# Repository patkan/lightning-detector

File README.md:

lightning-detector
==================

Lightning Detector ethernet sensor node and server based on AS3935 and ATmega328

by Virtex7 and patkan

<h3>Structure</h3>

server: Server-Software
    
pcb: KiCAD-Schematic and Layout

code: Code for the node

<h3>Aim</h3>

The aim of this project is to develop a network of sensors.
Those mainly detect lightning events, their intensity and distance.
As an addition the sensor nodes might capture weather data (light level, humidity, temperature, maybe pressure).

The captured data is then transferred to a single server together with a timestamp and the position of the node.
This server tries to determine the exact position of the lightning events by triangulation.
In further steps the server could generate maps and lists of lightning events.

The captured data shall be accessible to everyone without registration.
New sensors should be able to "join" the network by simply sending data to the server.
The server will provide the raw sensor data and the correlated values.
The complete project code (including microcontroller firmware and aggregation server) and board layout will be distributed under an open source license.

This project tries to be different from blitzortung.org. The code and layout shall be easily accesible.
The captured data shall be accessible for everyone (even if the user is not providing sensor data).
The hardware necessary for the absolute basic setup should not cost more than 25€ - 30€.
Everyone is free to use the data commercially, if desired.
However, it should be noted that no one can be taken liable for the correctness of the captured data.

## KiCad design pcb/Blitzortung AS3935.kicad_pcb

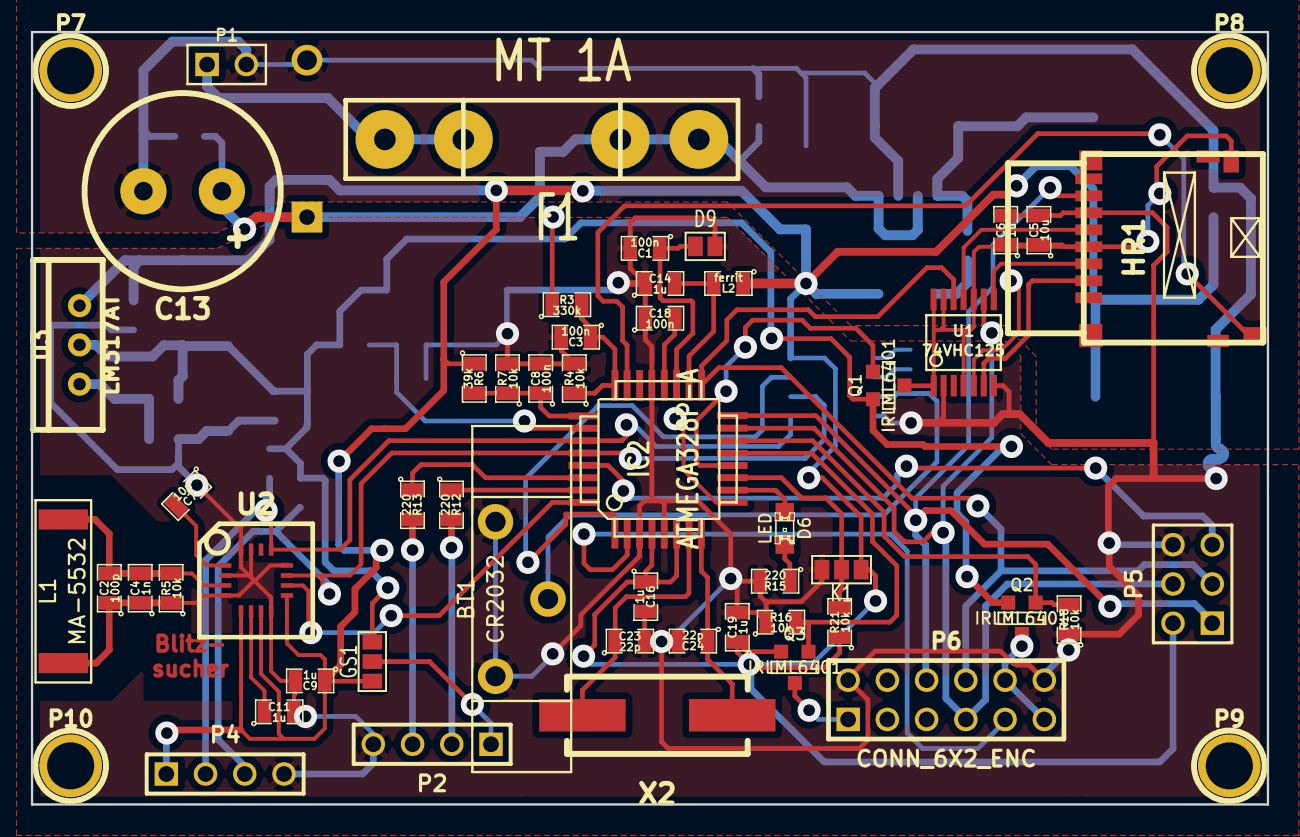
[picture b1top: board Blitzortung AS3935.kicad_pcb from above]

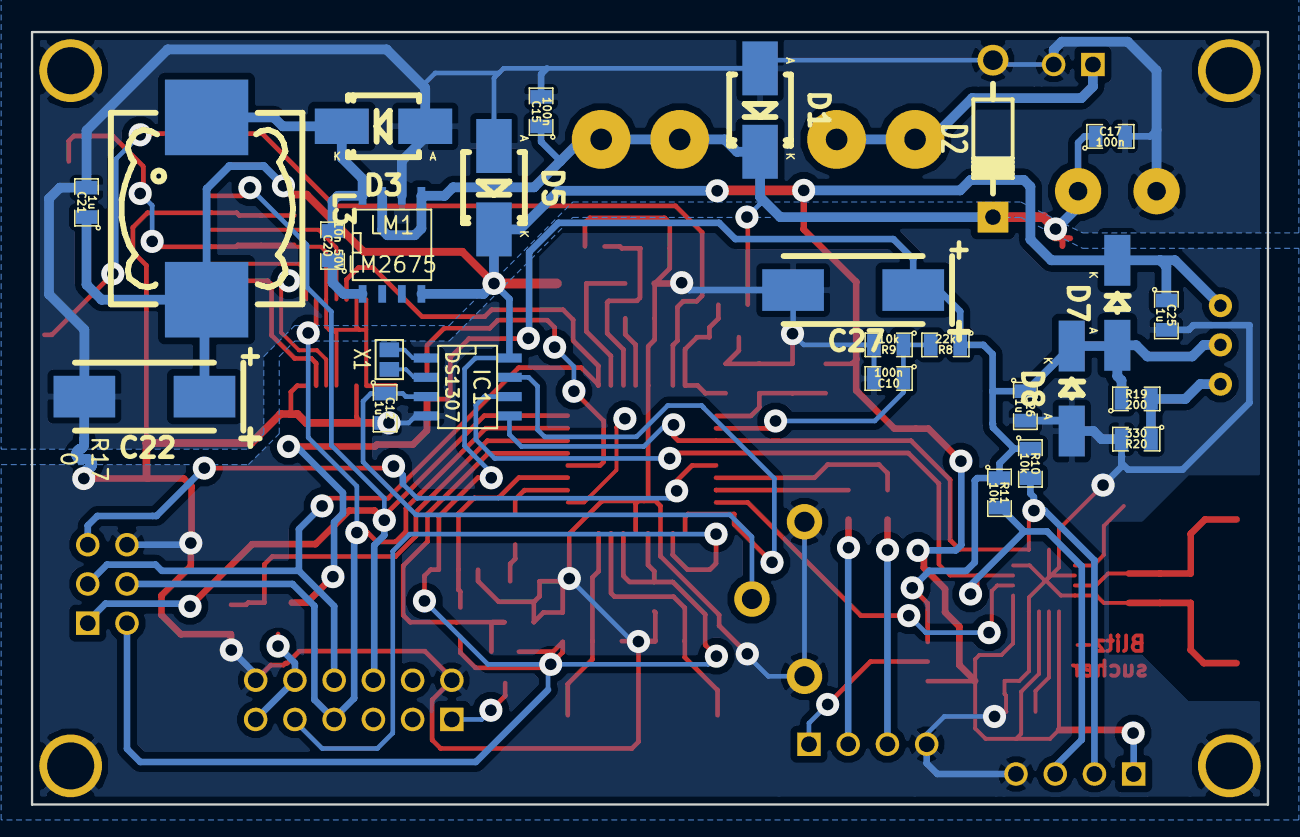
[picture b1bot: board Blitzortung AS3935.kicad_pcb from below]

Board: 2 copper layers, 80.0 x 50.0 mm, 81 parts (27 on the bottom side), 51 nets.

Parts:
BT1: CR2032; KHZ 20PCB-V
C1, C3, C8, C10, C15, C17, C18: 100n; SM0805
C2: 100p; SM0805
C4: 1n; SM0805
C5, C7: 10u; SM0805
C6, C9, C11, C12, C14, C16, C19, C21, C25, C26: 1u; SM0805
C13: 470u; Elko_vert_DM12-5_RM5
C20: 10n 50V; SM0805
C22, C27: 47u Tantal; TantalC_SizeD_EIA-7343_HandSoldering_RevA_28Aug2012
C23, C24: 22p; SM0805
D1: p6ke39aSMD; Diode-SMB_Handsoldering_RevA_27July2010
D2: SB150; Diode_DO-41_SOD81_Horizontal_RM10
D3: PMEG6030; Diode-SMB_Handsoldering_RevA_27July2010
D5: p6ke6,8aSMD; Diode-SMB_Handsoldering_RevA_27July2010
D6: LED; LED-0805
D7: 1n4148; Diode-MiniMELF_Handsoldering_RevA_27July2010
D8: zf3,6SMD; Diode-MiniMELF_Handsoldering_RevA_27July2010
D9: BPW34; GS2
F1: MT 1A; FUSE5-20
GS1: GS3
HR1: DM3D-SF
IC1: DS1307; SOIC-8_N
IC2: ATMEGA328P-A; TQFP32
K1: CONN_3_DHT; GS3
L1: MA-5532; MA5532-AE
L2: ferrit; SM0805
L3: 68uH; Choke_SMD_Wuerth-WE-PD-Typ-LS_Handsoldering_RevA_27July2010
LM1: LM2675; SO8N
P1: CONN_2_pwr; PIN_ARRAY_2X1
P2: CONN_4_GPS; PIN_ARRAY_4x1
P4: CONN_4_I2C; PIN_ARRAY_4x1
P5: CONN_3X2_ISP; pin_array_3x2
P6: CONN_6X2_ENC; pin_array_6x2
P7, P8, P9, P10: CONN_1; 1pin
Q1, Q2, Q3: IRLML6401; SOT23GDS
R3: 330k; SM0805
R4, R5, R7, R9, R10, R11, R16, R18, R21: 10k; SM0805
R6: 39k; SM0805
R8: 22k; SM0805
R12, R13, R15: 220; SM0805
R17: 0; MuSelf
R19: 200; SM0805
R20: 330; SM0805
U1: 74VHC125; SSOP-14
U2: AS3935; QFN-16-P
U3: LM317AT; TO220_VERT_123
X1: Uhrenquarz; GS2
X2: 20MHz; Crystal_HC49-SD_SMD_RevA_09Aug2010

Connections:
+3.3V: C26.1, C27.1, D7.1, D8.2, GS1.3, Q1.S, Q2.S, R8.1, R10.1, R11.1, R19.1, U3.2
+5V: C9.1, C16.1, C19.1, C21.1, C22.1, C25.1, D5.2, D7.2, GS1.1, IC1.8, IC2.4, IC2.6, K1.1, L2.1, L3.2, LM1.4, P4.1, P5.2, Q3.S, R6.1, R21.1, U2.5, U2.7, U2.9, U3.3
/IRQ_AS: IC2.32, U2.10
/IRQ_RTC: IC1.7, IC2.1
/IRQ_SD: HR1.10, IC2.23
/Vldr: C1.1, D9.1, IC2.19
/clk: HR1.5, U1.11
/cs: HR1.2, U1.6
/dht: IC2.11, K1.2, R21.2
/di: HR1.3, U1.8
/eth_3V: IC2.14, Q2.G, R18.2
/eth_5V: IC2.13, Q3.G, R16.2
/eth_cs: IC2.2, P6.9
/eth_res: P6.10, P6.11, Q2.D
/eth_sck: IC2.17, P5.3, P6.8, U1.12
/eth_si: IC2.15, P5.4, P6.7, U1.9
/eth_so: HR1.7, IC2.16, P5.1, P6.6
/mess3,3V: C10.1, IC2.26, R8.2, R9.1
/mess5V: C8.1, IC2.25, R6.2, R7.1
/messVin: C3.1, IC2.24, R3.2, R4.1
/reset: IC2.29, P5.5
/rxd: IC2.30, R13.1
/scl: IC1.6, IC2.28, P4.3, R11.2, U2.11
/sd3,3V: IC2.12, Q1.G
/sd_cs: IC2.9, U1.5
/sda: IC1.5, IC2.27, P4.2, R10.2, U2.13
/txd: IC2.31, R12.1
/xtal1: C23.1, IC2.7, X2.2
/xtal2: C24.1, IC2.8, X2.1
GND: BT1.2, C1.2, C2.1, C3.2, C4.1, C5.2, C6.2, C7.1, C8.2, C9.2, C10.2, C11.2, C12.2, C14.1, C16.2, C18.1, C19.2, C23.2, C24.2, C25.2, C26.2, C27.2, D8.1, D9.2, HR1.6, IC1.4, IC2.3, IC2.5, IC2.21, K1.3, L1.2, P2.4, P4.4, P5.6, P6.2, P6.12, P9.1, P10.1, R4.2, R5.1, R7.2, R9.2, R15.2, R16.1, R17.1, R18.1, R20.2, U1.2, U1.7, U2.2, U2.4, U2.8, U2.12, U2.15, U2.16
GNDPWR: C13.2, C15.2, C17.2, C21.2, C22.2, D1.1, D2.1, D3.1, D5.1, LM1.6, P1.2, P7.1, P8.1, R17.2
unnamed: BT1.1, C12.1, IC1.3
unnamed: C2.2, C4.2, L1.1, R5.2, U2.3
unnamed: C7.2, U2.1
unnamed: C11.1, U2.6
unnamed: C13.1, C15.1, C17.1, D1.2, D2.2, F1.2, LM1.5, LM1.7, R3.1
unnamed: C14.2, IC2.18, L2.2
unnamed: C18.2, IC2.20
unnamed: C20.1, LM1.1
unnamed: C20.2, D3.2, L3.1, LM1.8
unnamed: D6.1, IC2.10
unnamed: D6.2, R15.1
unnamed: F1.1, P1.1
unnamed: GS1.2, P2.1
unnamed: IC1.1, X1.2
unnamed: IC1.2, X1.1
unnamed: P2.2, R12.2
unnamed: P2.3, R13.2
unnamed: P6.1, Q3.D
unnamed: R19.2, R20.1, U3.1
VCC: C5.1, C6.1, HR1.4, HR1.9, Q1.D, U1.1, U1.4, U1.10, U1.13, U1.14

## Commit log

2013-11-07 Update README.md
    Grobe Übersicht angelegt
2013-11-07 base structure for project
2013-11-07 ideas for the project
2013-11-08 new CAD Files for lightning-detector, in progress....
2013-11-08 added Antenna
2013-11-08 AGC to ACG
2013-11-08 ignoring .ps and .bak files from KiCAD
2013-11-08 Directory for app notes, datasheets and other ressources
2013-11-08 datasheets of antenna and detector chip
2013-11-08 Atmel datasheet
2013-11-08 typo in filename
2013-11-08 added datasheet for the ethernet controller
2013-11-08 new ideas
2013-11-08 Update brainstorming.txt
    -Board sollte sich automatisch kofigurieren
    -Erzeugung eines eigenen Wetterfeeds anhand der Daten der eigenen Station
2013-11-08 new Ideas and more schematic - will be done soon...
2013-11-08 typos...
2013-11-08 datasheet for DHT11
2013-11-08 schlechtes datasheet of DHT22
2013-11-08 new datasheet for the 5V switchmode converter and more schematic....
2013-11-08 additional test leds and sensor connectors
2013-11-09 some changes.....
2013-11-09 selected inductors and diodes...
2013-11-09 LDR-Messschaltung hinzugefügt
2013-11-09 Beschriftung des LDR
2013-11-09 LDR-Spannungsteiler aktualisiert
2013-11-09 added one sick capacitor :D
2013-11-09 switching mosfets for the ENC28J60 for energy saving :D
2013-11-09 minor label corrections
2013-11-09 more realistic pricing
2013-11-09 input, 5V and 3,3V voltage measurement added
2013-11-09 added two datasheets...
2013-11-09 datasheet for SD-Card slot
2013-11-10 crystal datasheet
2013-11-10 datasheet for buffer for SD-Card
2013-11-10 added SD-Card, real time clock and some small things....
2013-11-10 changed ground plane for the 3,3V LDO to standard ground
2013-11-10 sd card signal converter added.
2013-11-10 changed crystal from 16MHz to 20MHz because I can.
2013-11-10 generated netlist and ran the electric rules check. no ERC errors.
2013-11-10 footprint for DM3d-SF -- needs to be revised and enhanced
2013-11-10 enhanced footprint
2013-11-10 new datasheets and changes in the .pro-file only missing footprint: the sd card slot!
2013-11-10 new gitignore will block cache and autosave-files
2013-11-10 new TO-220 socket for the lm317 voltage regulator
2013-11-10 footprints and libs for battery holder and sdcard now up to date and included in schematic
2013-11-10 footprint for QFN.Quark
2013-11-10 first layoutfile (with no layout in it, but created...) and even more datasheets..
2013-11-10 changed LDR to photodiode in schematic
2013-11-10 added the qfn16 lib from patkan and converted it to a .mod file.
2013-11-10 changes :D
2013-11-16 first attempt of layout - many many VIAs but still home-made manufacturing possible. you have to connect the SC_CS wire with a bridge on a virtual third layer. no warranty....
2013-11-18 Update brainstorming.txt
    Messung des Erdmagnetfeldes?
2013-11-22 Update brainstorming.txt
    Link to done project with this chip
